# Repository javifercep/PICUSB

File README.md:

PICUSB
======

Generic USB board for teaching purpose

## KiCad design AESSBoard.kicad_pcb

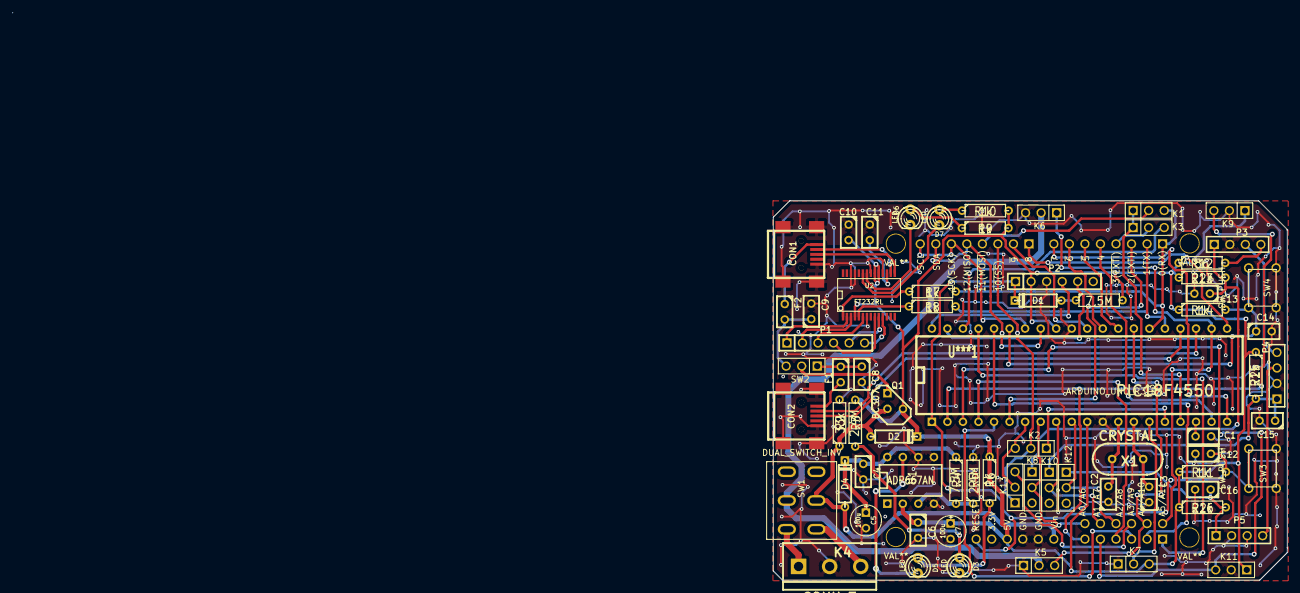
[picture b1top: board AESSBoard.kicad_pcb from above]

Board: 2 copper layers, 208.4 x 92.8 mm, 75 parts (0 on the bottom side), 78 nets.

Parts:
3MMDRILL, 3MMDRILL#2, 3MMDRILL#3, 3MMDRILL#4: VAL**; 3MMDRILL
C1, C4, C6, C8, C9, C10, C11, C12, C13, C14, C15, C16: 100n; C1
C2: 15P; C1
C3: 15p; C1
C5, C7: 100u; C1V5
CON1, CON2: USBMINIB; USB_MINI_B_AESS
D1, D2, D4: DIODE; D3
D3, D5, D6, D7: LED; LED-3MM
F1, F2: FUSE; C1
K1, K2, K3, K5, K6, K7, K8, K9, K10, K11, K12, K13: CONN_3; PIN_ARRAY_3X1
K4: CONN_3; bornier3
P1, P2: CONN_6; PIN_ARRAY-6X1
P3, P4, P5: CONN_4; PIN_ARRAY_4x1
Q1: BC307; TO92-EBC
R1, R4: 7,5M; R3
R2: 33k; R3
R3, R5: 2,4M; R3
R6, R7, R8, R9, R10, R11, R14: 1k; R3
R12: 56; R3
R13, R15, R16: 22k; R3
SW1: DUAL_SWITCH_INV; AESS_SWITCH
SW2: SWITCH_INV; PIN_ARRAY_3X1
SW3, SW4: SW_PUSH; AESS_PUSH_BUTTON
U1: ADP667AN; DIP-8__300
U2: FT232RL; SSOP28
U3: ARDUINO_UNO_R3_EX; ArduinoUNOShieldR3EX
U***1: PIC18F4550; DIP-40__600
X1: CRYSTAL; HC-49V

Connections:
/D3: K3.3, U***1.38
/ICSPCLK: P2.5, U***1.39
/ICSPDATA: P2.4, U***1.40
/IOExtension/5V0: C6.1, C7.1, C10.2, D2.2, K7.3, K9.1, K11.1, P2.2, Q1.C, R1.2, R3.1, R6.1, R9.2, R10.2, R11.1, R12.1, R13.1, R14.1, R15.1, R16.1, U1.2, U2.4, U2.19, U2.20, U3.22, U***1.11, U***1.32
/IOExtension/A6: C13.1, K8.1, P3.1, R13.2
/IOExtension/A7: C15.1, K10.1, P4.1, R15.2
/IOExtension/A8: C16.1, K12.1, P5.1, R16.2
/IOExtension/AN0: K9.3, U3.19, U***1.2
/IOExtension/AN1: K11.3, U3.18, U***1.3
/IOExtension/AN2: U3.17, U***1.4
/IOExtension/AN3: U3.16, U***1.5
/IOExtension/AN4: U3.15, U***1.36
/IOExtension/AN5: U3.14, U***1.37
/IOExtension/AN6: K8.2, U3.28, U***1.8
/IOExtension/AN7: K10.2, U3.29, U***1.9
/IOExtension/AN8: K12.2, U3.30, U***1.10
/IOExtension/AN9: K13.3, U3.31
/IOExtension/AN10: K5.3, U3.32, U***1.27
/IOExtension/AN11: K6.1, U3.33, U***1.22
/IOExtension/BOOT: K7.2, U***1.15
/IOExtension/D2: U3.2, U***1.6
/IOExtension/D3: K3.2, U3.3
/IOExtension/D4: U3.4, U***1.19
/IOExtension/D5: U3.5, U***1.28
/IOExtension/D6: U3.6, U***1.29
/IOExtension/D7: U3.7, U***1.20
/IOExtension/D8: U3.8, U***1.21
/IOExtension/D9: U3.9, U***1.30
/IOExtension/MISO: U3.12, U3.26, U***1.33
/IOExtension/MOSI: K1.2, U3.11
/IOExtension/RESET: C12.1, D1.2, P2.1, R11.2, SW3.1, U3.24, U***1.1
/IOExtension/SCK: U3.13, U3.27, U***1.34
/IOExtension/SS: K2.2, K13.1, U3.10
/IOExtension/USER_BUTTON: C14.1, R14.2, SW4.1, U***1.35
/IOExtension/VMOT: K5.2, K6.2, SW1.5
/OSC1: C2.2, U***1.13, X1.2
/OSC2: C3.2, U***1.14, X1.1
/PWM1: K1.1, K3.1, U***1.17
/PWM5: K2.1, U***1.16
/Power/VEXT: D2.1, D4.1, Q1.B, R2.1, SW1.2, U3.20
/SS/A9: K2.3, K13.2, U***1.7
/USB/RSRx: K1.3, R7.2, U3.0, U***1.26
/USB/RSTx: R8.2, U3.1, U***1.25
/USB/USBDM: CON2.2, U***1.23
/USB/USBDP: CON2.3, U***1.24
/USB/VUSB: Q1.E, SW2.2
/USB/Vusbpure: C8.1, F1.1, SW2.1
/USB/Vusbserie: C9.1, F2.2, SW2.3
GND: C1.2, C2.1, C3.1, C4.2, C5.2, C6.2, C7.2, C8.2, C9.2, C10.1, C11.1, C12.2, C13.2, C14.2, C15.2, C16.2, CON1.5, CON1.6, CON1.7, CON1.8, CON1.9, CON2.5, CON2.6, CON2.7, CON2.8, CON2.9, D3.2, K4.2, K5.1, K6.3, K7.1, K9.2, K11.2, P2.3, P3.2, P4.2, P5.2, P5.3, R2.2, R5.2, SW3.2, SW4.2, U1.4, U1.5, U1.6, U2.7, U2.18, U2.21, U2.25, U2.26, U3.21, U3.25, U***1.12, U***1.31
unnamed: C1.1, U***1.18
unnamed: D3.1, R3.2
unnamed: D1.1, R1.1
unnamed: R4.2, R5.1, U1.3
unnamed: K4.1, SW1.4
unnamed: K4.3, SW1.1
unnamed: D5.1, R6.2
unnamed: C4.1, C5.1, D4.2, R4.1, U1.8
unnamed: D5.2, U1.7
unnamed: P1.2, U2.3
unnamed: P1.1, U2.2
unnamed: D6.1, R9.1
unnamed: P1.3, U2.6
unnamed: P1.4, U2.9
unnamed: P1.5, U2.10
unnamed: D6.2, U2.22
unnamed: R8.1, U2.5
unnamed: D7.2, U2.23
unnamed: D7.1, R10.1
unnamed: P1.6, U2.11
unnamed: R7.1, U2.1
unnamed: CON1.1, F2.1
unnamed: CON1.2, U2.16
unnamed: CON1.3, U2.15
unnamed: CON2.1, F1.2
unnamed: C11.2, U2.17
unnamed: P3.4, R12.2
unnamed: P4.3, P5.4
unnamed: P3.3, P4.4

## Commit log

2014-12-24 Revision 0.0
